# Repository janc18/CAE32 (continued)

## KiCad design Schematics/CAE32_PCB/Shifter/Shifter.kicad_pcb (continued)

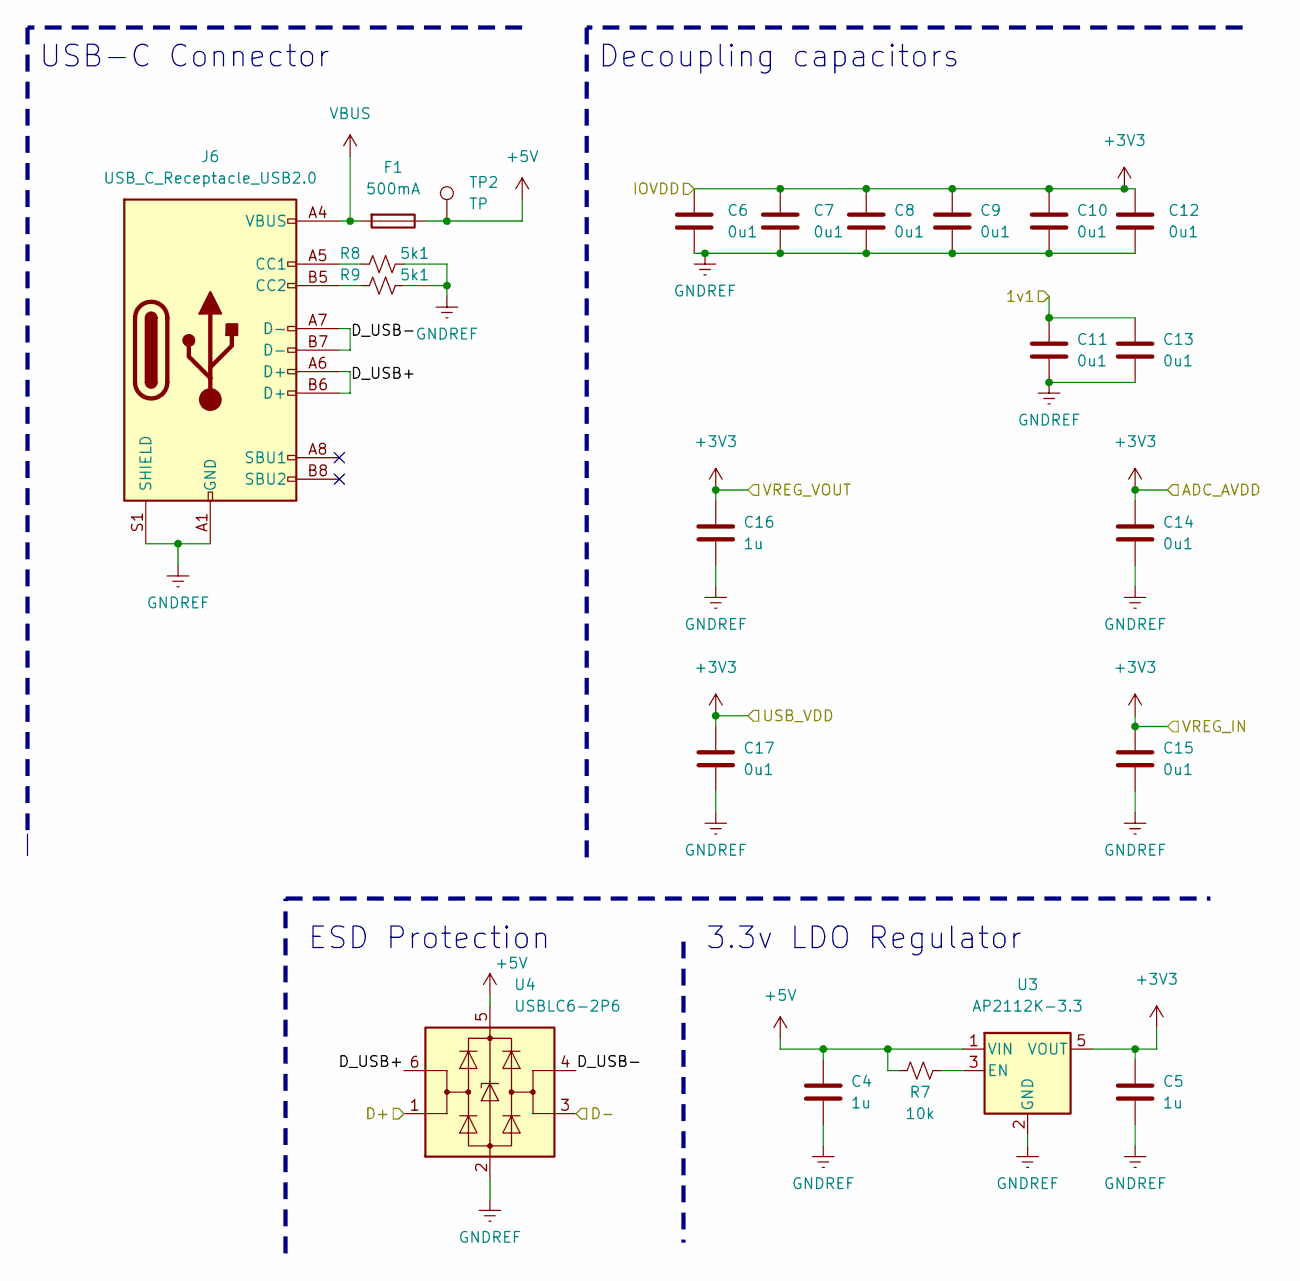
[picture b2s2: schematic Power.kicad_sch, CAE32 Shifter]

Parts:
C4, C5, C16: 1u; C_01005_0402Metric
C6, C7, C8, C9, C10, C11, C12, C13, C14, C15, C17: 0u1; C_01005_0402Metric
F1: 500mA; Fuse_0603_1608Metric
J6: USB_C_Receptacle_USB2.0; USB_C_Receptacle_Palconn_UTC16-G
R7: 10k; R_0402_1005Metric
R8, R9: 5k1; R_0402_1005Metric
TP2: TP; TestPoint_Pad_D1.0mm
U3: AP2112K-3.3; SOT-23-5
U4: USBLC6-2P6; SOT-666

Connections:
+3V3: C5.1, C6.1, C7.1, C8.1, C9.1, C10.1, C12.1, C14.1, C15.1, C16.1, C17.1, U3.5 (VOUT); also elsewhere on the board
+5V: C4.1, F1.1, R7.2, TP2.1, U3.1 (VIN), U4.5 (VBUS)
/Power/1v1: C11.1, C13.1; also elsewhere on the board
/Power/D+: U4.1 (I/O1); also elsewhere on the board
/Power/D-: U4.3 (I/O2); also elsewhere on the board
/Power/D_USB+: J6.A6 (D+), J6.B6 (D+), U4.6 (I/O1)
/Power/D_USB-: J6.A7 (D-), J6.B7 (D-), U4.4 (I/O2)
GNDREF: C4.2, C5.2, C6.2, C7.2, C8.2, C9.2, C10.2, C11.2, C12.2, C13.2, C14.2, C15.2, C16.2, C17.2, J6.A1 (GND), J6.A12 (GND), J6.B1 (GND), J6.B12 (GND), J6.S1 (SHIELD), R8.1, R9.1, U3.2 (GND), U4.2 (GND); also elsewhere on the board
unnamed: J6.A5 (CC1), R8.2
unnamed: J6.B5 (CC2), R9.2
unnamed: R7.1, U3.3 (EN)
VBUS: F1.2, J6.A4 (VBUS), J6.A9 (VBUS), J6.B4 (VBUS), J6.B9 (VBUS)

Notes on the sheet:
USB-C Connector
3.3v LDO Regulator
ESD Protection
Decoupling capacitors

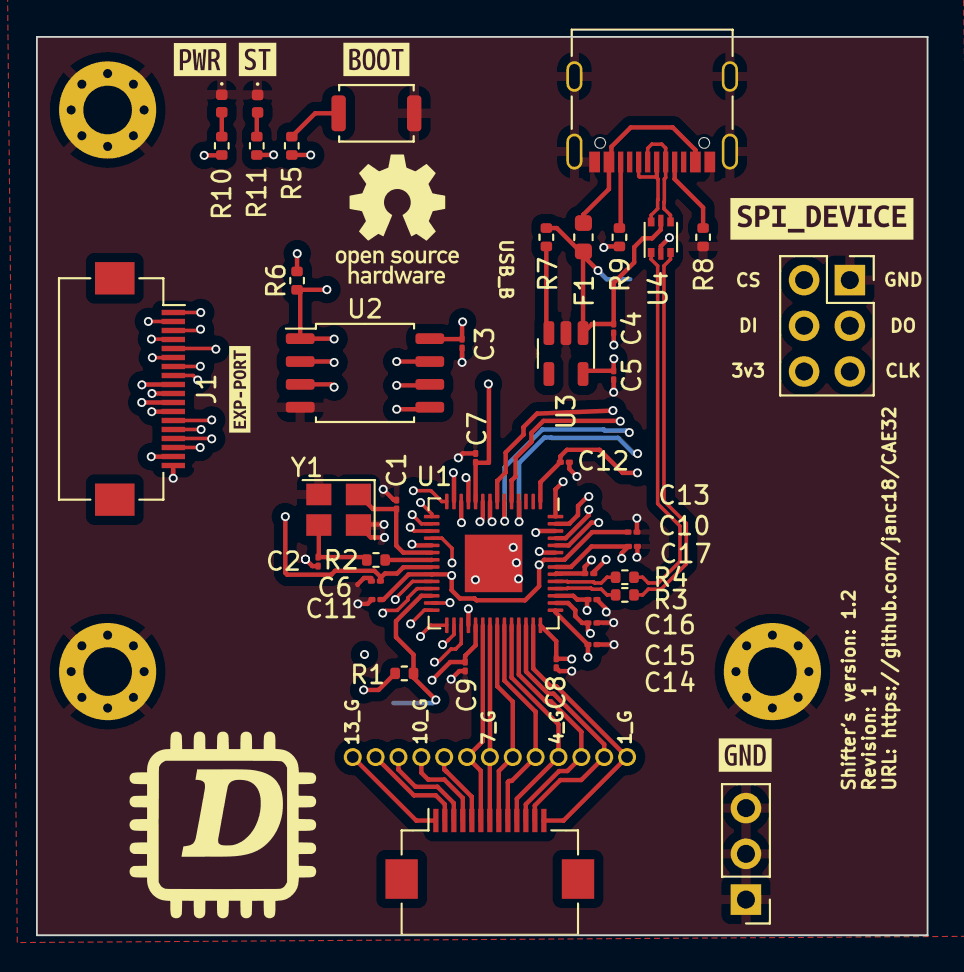
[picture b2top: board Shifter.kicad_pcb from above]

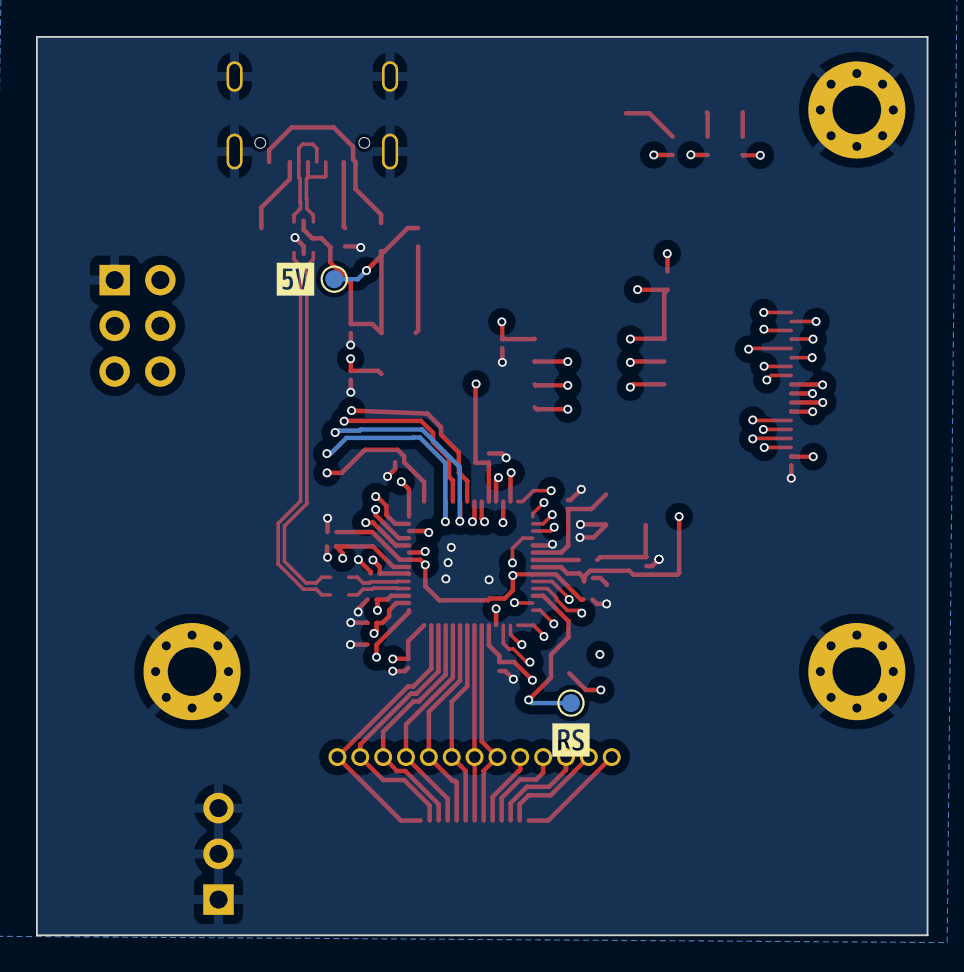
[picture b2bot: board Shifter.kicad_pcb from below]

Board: 4 copper layers, 49.5 x 49.9 mm, 56 parts (4 on the bottom side), 57 nets.

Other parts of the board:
kibuzzard-64B75D82: G***; kibuzzard-64B75D82
kibuzzard-64B759C0: G***; kibuzzard-64B759C0
kibuzzard-6511E845: G***; kibuzzard-6511E845
kibuzzard-6511E886: G***; kibuzzard-6511E886
kibuzzard-6517AD32: G***; kibuzzard-6517AD32
kibuzzard-6518B6F6: G***; kibuzzard-6518B6F6
kibuzzard-651234A4: G***; kibuzzard-651234A4
kibuzzard-651234C4: G***; kibuzzard-651234C4

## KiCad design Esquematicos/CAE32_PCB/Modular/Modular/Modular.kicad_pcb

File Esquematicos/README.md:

# Placa de constrol principal CAE32

## Como microcontrolador principal se usará el ESP-32-S3

Debido a que este cuenta con la funcionalidad OTG "On The Go", con lo cual ya no es necesario hardware extra 
para hacer la conexión.

## Elementos

* Puerto Usb tipo C para conectarlo a la Pc.

* Alimentación proveniente de Pc.

* Multiplexores.
	- Para conmutar entre las entradas analógicas y digitales, provenientes de los sensores de posicion de pedales e
interruptores correspondientes al valor de la marcha.

* ADC
	- Para obtener una mayor presición se usara un ADC externo en conjunto con el multiplexor y leer las entradas
analógicas una a la vez.

* Pines sobrantes expuestos, debido que aún es un prototipo. 

## Microcontrolador secundario

Este MCU se conectara con el microcontrolador principal por medio de UART, para controlar accesorios o incluso 
reducirle la carga al ESP32-S3, manipulando y formateando valores.

Ademas de tener todos los pines expuestos. 

## Controlador de potencia para el nema 34

Este se encontrara en otra PCB, y las señales seran producidas por el ESP32-S3 o por el MCU secundario.

## PCBs para los pedales

Se cambiara el AS5600 por un sensor de efecto Hall, así que será necesario fabricar una pequeña PCB, para sujetarlo
en su lugar y filtrar la señal en caso que se requiera

## Descripción detallada de componentes

* PCB
Para programar los dos MCU, se usará un USB-UART en caso del ESP32-S3 y Stlink para el MCU de STM

1. ESP32-S3-WROOM-1-N4 [Guía para diseño del hardware del ESP32-S3](https://www.espressif.com/sites/default/files/documentation/esp32-s3_hardware_design_guidelines_en.pdf)

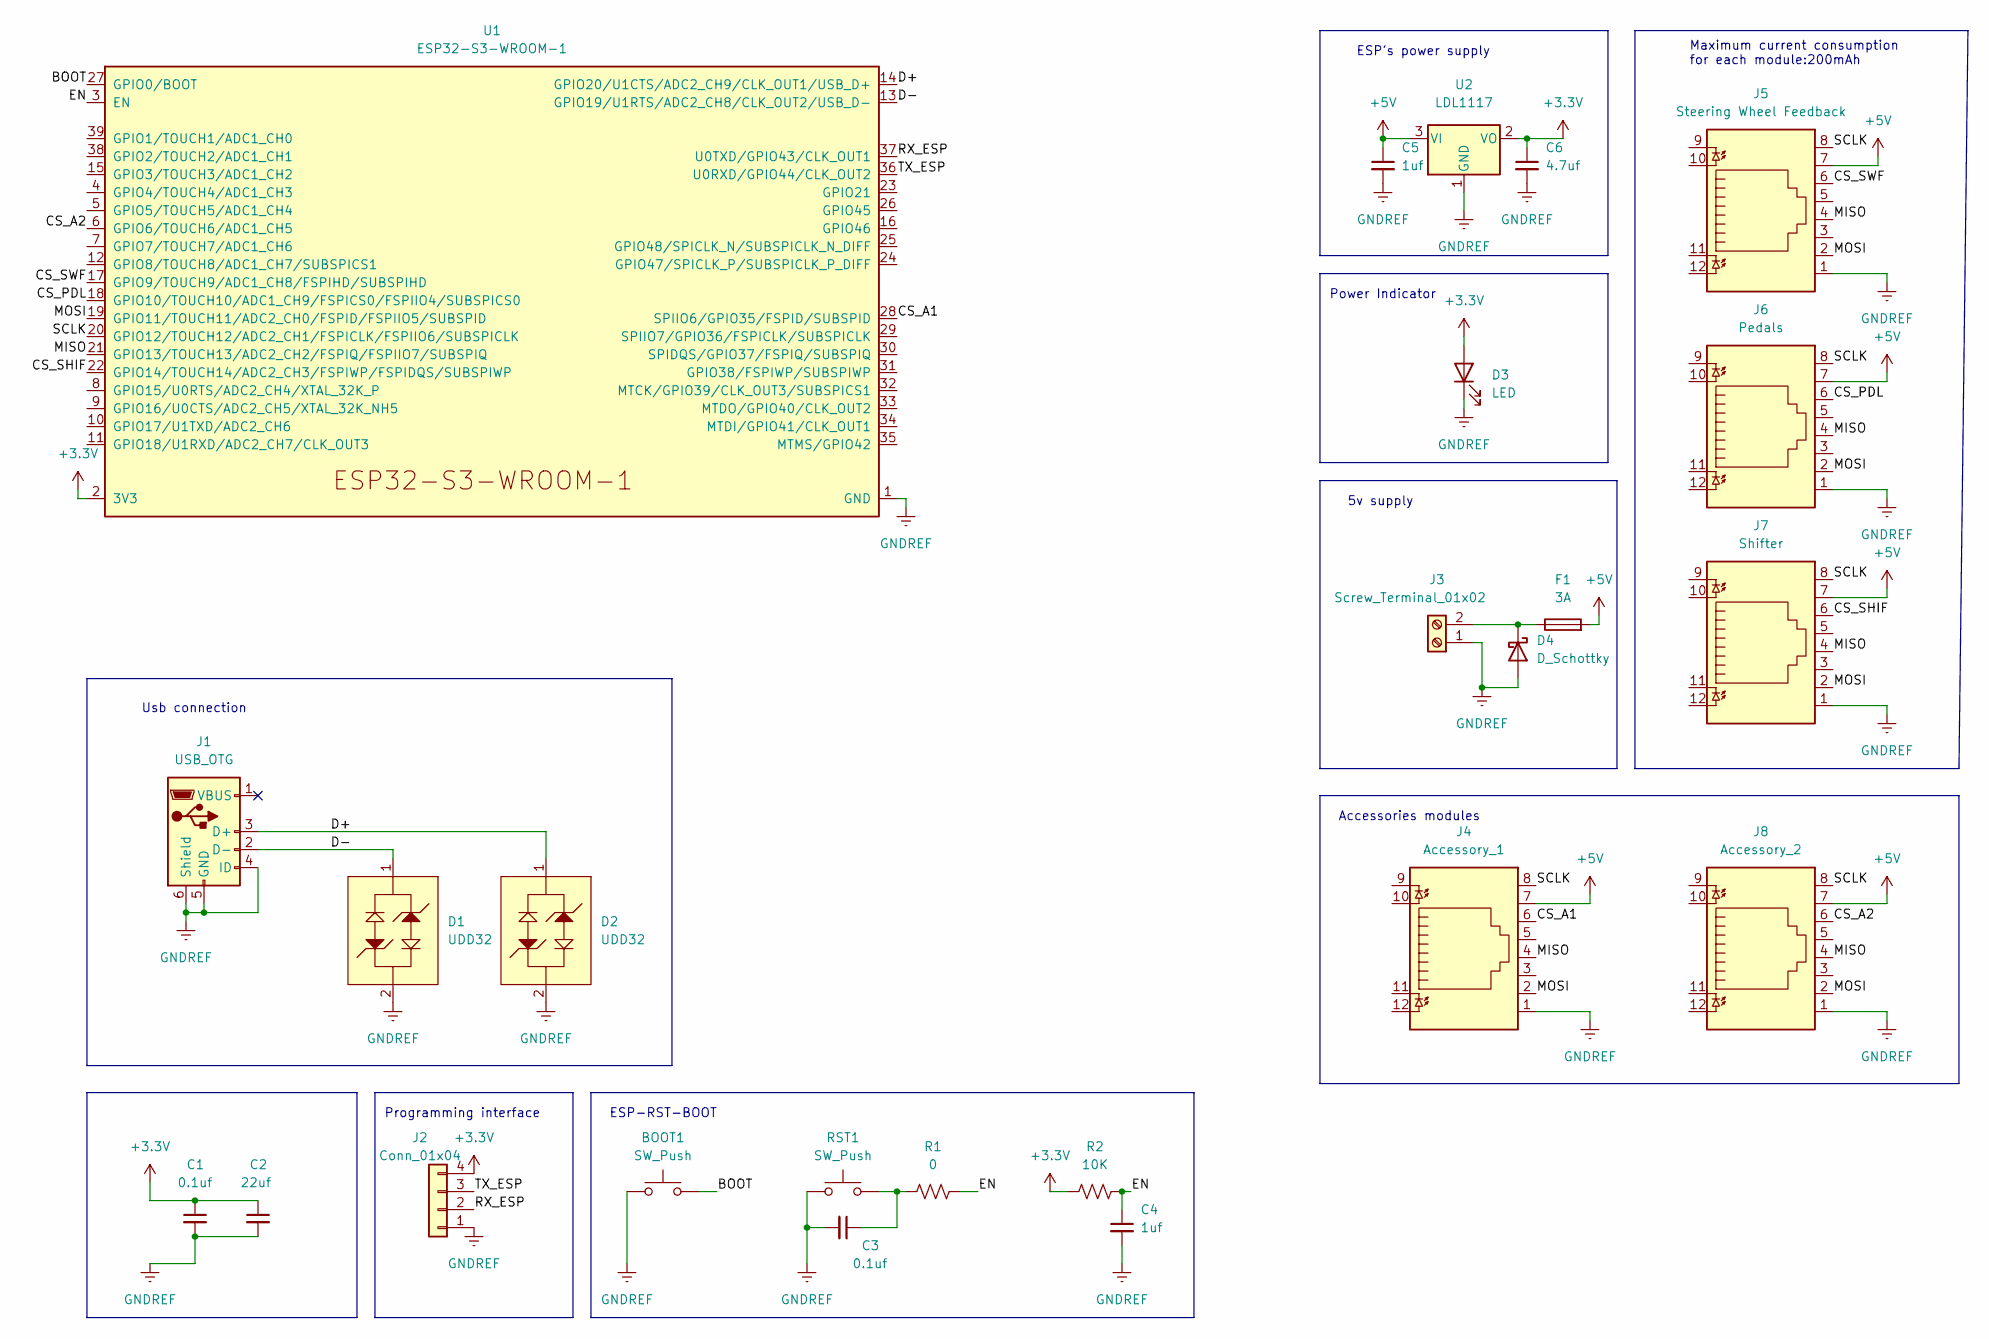
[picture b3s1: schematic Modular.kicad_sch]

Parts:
BOOT1: SW_Push; SW_Push_1P1T_NO_CK_KSC6xxJ
C1, C3: 0.1uf; C_0805_2012Metric_Pad1.18x1.45mm_HandSolder
C2: 22uf; C_0805_2012Metric_Pad1.18x1.45mm_HandSolder
C4, C5: 1uf; C_0805_2012Metric_Pad1.18x1.45mm_HandSolder
C6: 4.7uf; C_0805_2012Metric_Pad1.18x1.45mm_HandSolder
D1, D2: UDD32
D3: LED; LED_0805_2012Metric_Pad1.15x1.40mm_HandSolder
D4: D_Schottky; D_SMA_Handsoldering
F1: 3A; Fuse_1812_4532Metric_Pad1.30x3.40mm_HandSolder
J1: USB_OTG; USB_Micro-B_Amphenol_10104110_Horizontal
J2: Conn_01x04; PinHeader_1x04_P2.54mm_Vertical
J3: Screw_Terminal_01x02; TerminalBlock_bornier-2_P5.08mm
J4: Accessory_1; RJ45_Amphenol_RJHSE538X
J5: Steering Wheel Feedback; RJ45_Amphenol_RJHSE538X
J6: Pedals; RJ45_Amphenol_RJHSE538X
J7: Shifter; RJ45_Amphenol_RJHSE538X
J8: Accessory_2; RJ45_Amphenol_RJHSE538X
R1: 0; R_0805_2012Metric_Pad1.20x1.40mm_HandSolder
R2: 10K; R_0805_2012Metric_Pad1.20x1.40mm_HandSolder
RST1: SW_Push; SW_Push_1P1T_NO_CK_KSC6xxJ
U1: ESP32-S3-WROOM-1
U2: LDL1117; SOT-223-3_TabPin2

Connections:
+3.3V: C1.1, C2.1, C6.1, D3.2 (A), J2.4, R2.1, U1.2 (3V3), U2.2 (VO)
+5V: C5.1, F1.2, J4.7, J5.7, J6.7, J7.7, J8.7, U2.3 (VI)
/BOOT: BOOT1.2, U1.27 (GPIO0/BOOT)
/CS_A1: J4.6, U1.28 (SPIIO6/GPIO35/FSPID/SUBSPID)
/CS_A2: J8.6, U1.6 (GPIO6/TOUCH6/ADC1_CH5)
/CS_PDL: J6.6, U1.18 (GPIO10/TOUCH10/ADC1_CH9/FSPICS0/FSPIIO4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)
/CS_SHIF: J7.6, U1.22 (GPIO14/TOUCH14/ADC2_CH3/FSPIWP/FSPIDQS/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)
/CS_SWF: J5.6, U1.17 (GPIO9/TOUCH9/ADC1_CH8/FSPIHD/SUBSPIHD)
/D+: D2.1, J1.3 (D+), U1.14 (GPIO20/U1CTS/ADC2_CH9/CLK_OUT1/USB_D+)
/D-: D1.1, J1.2 (D-), U1.13 (GPIO19/U1RTS/ADC2_CH8/CLK_OUT2/USB_D-)
/EN: C4.1, R1.2, R2.2, U1.3 (EN)
/MISO: J4.4, J5.4, J6.4, J7.4, J8.4, U1.21 (GPIO13/TOUCH13/ADC2_CH2/FSPIQ/FSPIIO7/S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)
/MOSI: J4.2, J5.2, J6.2, J7.2, J8.2, U1.19 (GPIO11/TOUCH11/ADC2_CH0/FSPID/FSPIIO5/S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)
/RX_ESP: J2.2, U1.37 (U0TXD/GPIO43/CLK_OUT1)
/SCLK: J4.8, J5.8, J6.8, J7.8, J8.8, U1.20 (GPIO12/TOUCH12/ADC2_CH1/FSPICLK/FSPIIO6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)
/TX_ESP: J2.3, U1.36 (U0RXD/GPIO44/CLK_OUT2)
GNDREF: BOOT1.1, C1.2, C2.2, C3.2, C4.2, C5.2, C6.2, D1.2, D2.2, D3.1 (K), D4.2 (A), J1.4 (ID), J1.5 (GND), J1.6 (Shield), J2.1, J3.1, J4.1, J5.1, J6.1, J7.1, J8.1, RST1.1, U1.1 (GND), U1.40 (GND), U1.41 (GND), U2.1 (GND)
unnamed: C3.1, R1.1, RST1.2
unnamed: D4.1 (K), F1.1, J3.2

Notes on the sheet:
Maximum current consumption for each module:200mAh
Power Indicator
Usb connection
Accessories modules
5v supply
Programming interface
ESP's power supply
ESP-RST-BOOT

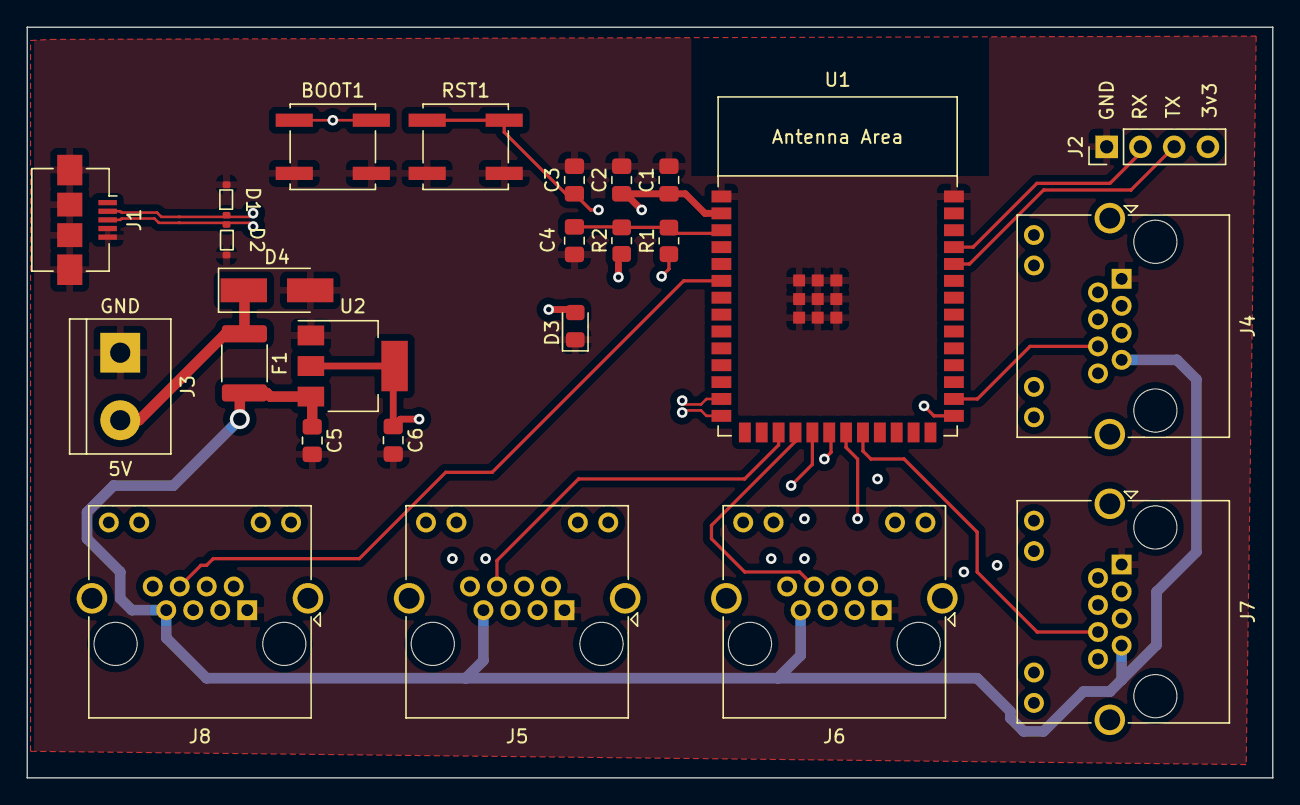
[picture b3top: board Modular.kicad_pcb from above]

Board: 4 copper layers, 93.8 x 56.5 mm, 25 parts (0 on the bottom side), 19 nets.

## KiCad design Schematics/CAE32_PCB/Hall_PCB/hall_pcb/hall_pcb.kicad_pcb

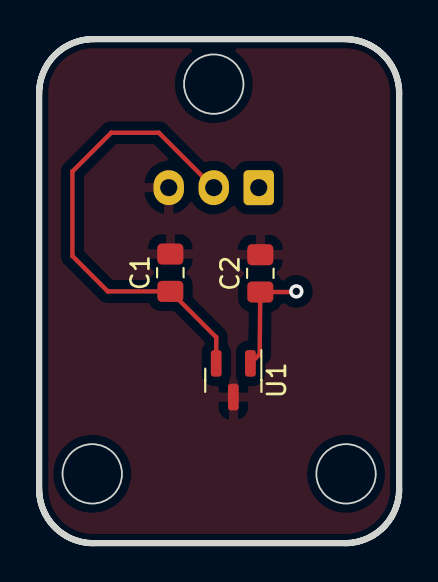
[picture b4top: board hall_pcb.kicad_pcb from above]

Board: 2 copper layers, 20.0 x 28.0 mm, 4 parts (1 on the bottom side), 3 nets.

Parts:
C1: 4.7nf; C_0805_2012Metric_Pad1.18x1.45mm_HandSolder
C2: 100nf; C_0805_2012Metric_Pad1.18x1.45mm_HandSolder
J1: Conn_01x03_Female; JST_EH_B3B-EH-A_1x03_P2.50mm_Vertical
U1: MT9105ET; SOT-23

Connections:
+3V3: C2.1, J1.1, U1.1 (VCC)
/Vout: C1.1, J1.2, U1.2 (OUTPUT)
GNDREF: C1.2, C2.2, J1.3, U1.3 (GND)

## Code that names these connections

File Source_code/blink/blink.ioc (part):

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Mcu.Name=STM32F072R(8-B)Tx
Mcu.Package=LQFP64
Mcu.UserName=STM32F072RBTx
PA11.Mode=Device
PA11.Signal=USB_DM
PA12.Mode=Device
PA12.Signal=USB_DP
PA2.Signal=GPIO_Output
PA4.GPIOParameters=GPIO_Label
PA4.GPIO_Label=CS
PA4.Signal=GPIO_Output
PA5.GPIOParameters=GPIO_Label
PA5.GPIO_Label=SCLK
PA5.Signal=GPIO_Output
PA6.GPIOParameters=GPIO_Label
PA6.GPIO_Label=MISO
PA6.Signal=GPIO_Input
PA7.GPIOParameters=GPIO_Label
PA7.GPIO_Label=MOSI
PA7.Signal=GPIO_Output
PC0.Signal=GPIO_Output
PC1.Signal=GPIO_Output
PC2.Signal=GPIO_Output
PF0-OSC_IN.Mode=HSE-External-Oscillator
PF0-OSC_IN.Signal=RCC_OSC_IN
PF1-OSC_OUT.Mode=HSE-External-Oscillator
PF1-OSC_OUT.Signal=RCC_OSC_OUT
RCC.SYSCLKFreq_VALUE=48000000
RCC.SYSCLKSource=RCC_SYSCLKSOURCE_PLLCLK
board=custom

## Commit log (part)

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2023-06-16 Primer commit
2023-06-17 delete: se elimina libreria json-c de archivo CMakeLists
2023-06-17 add: Archivo Makefile, para ejecutar la construcción de la gui
2023-06-17 update: README, con las nuevas caracteristicas de la PCB de pedales version
2023-06-17 chore: se corrigen valores de referencias de componentes, creación de nuevas hojas de diagramas, mejor distribución de componentes
2023-06-17 add: hoja de esquematicos de conexiones de alimentacion
2023-06-18 add: imagen con función de cada pin
2023-06-18 update: se añade otra hoja para las celdas de carga, ademas de reorganizar todas las hojas
2023-06-18 update: se agrega instrucciones para la compilacion de la GUI usando docker
2023-06-19 update: Se nombran los pines con sus funciones
2023-06-20 add: se crea archivo idf_component.yml con la depencia necesaria (esp_tinyusb)
2023-06-20 fix: se corrige el nombre de la depencia en require de tinyusb->esp_tinyusb, ademas de añadir las depencia de freertos
2023-06-20 chore: se corrige el estilo de codigo
2023-06-20 delete: component.mk, ya que no es necesario
2023-06-21 update: se agrega el consumo de corriente a los IC's ademas de agregar el URL y numero de parte de los componentes de LCSC en kicad
2023-06-21 add: archivo de contribución en español
2023-06-21 add: se añade nueva regla para contruir la gui
2023-06-21 Update README.md
    remove: imagen de PCB terminada
2023-06-22 add: imagen de logo de oshw y easter egg
2023-06-25 add: nuevas reglas de archivos gerber, csv, xml y .log
2023-06-25 add: se añade un fusible extra para proteger el circuito de 5v al regulador de voltage de 3v3
2023-06-25 update: README.md con imagen de la version 2 de PCB para los pedales
2023-06-26 update: se agrega via stitching a la pcb de los pedales
2023-07-12 delete: archivos innecesarios
2023-07-12 add:makefile para construir el firmware usando docker
2023-07-16 add: nueva regla para los realeases de archivos de frabricacion pcb
2023-07-21 update: se enruta completamente la pcb, aunque aun necesario un análisis posterior, ademas de agregar huellas e imagen de la pcb completa
2023-09-16 update: changed the castelled holes for pin sockets and changed 0603 footprints to 0402
2023-09-20 update: added templates files for the devolpment of a Feedback PCB
2023-09-20 chore: arrange of schematic elements
2023-09-24 update: new desing for the PCB edgecuts
2023-09-27 update: added new information about the pcb updates, and created another README file in English
2023-09-27 update: added a new rule to exclude new realeses
2023-09-27 update: added minor improvements to Pedal's PCB
2023-09-27 add: new rule for lck files
2023-10-01 update: redesign of the shifter PCB, changing the PCB requirements(via from 0.15 to 0.3mm) and pin sockets for FCP connectors
2023-10-02 remove: deleted README file in the "Esquematicos" folder because is irrelevant
2023-10-02 update: Device simulation's README file changed to English
2023-10-02 update: ESP32-S3's README file changed to English
2023-10-03 test: testing Github Actions to test the GUI compilation
2023-10-29 chore: update README, added PCB result image
2023-11-06 chore: update README with the overall status of the project
2023-11-27 add: UML use cases draft using the umbrellon software
2023-11-29 update: finished UML use cases diagram
2023-11-29 add: UML use cases image
2023-12-01 chore: added two new "Section" with a brief function resume and a Pcb issues
2023-12-16 deleted: umbrello file for the generation of an UML diagram
2023-12-16 chore: added file to write notes about the whole project
2023-12-16 chore: creation of a file to take notes about the how can be implement the TDD to the project
2023-12-18 add: a simple c code that print a string from another path
2023-12-18 add: c code that compare a string
2023-12-18 add: cmake file for future device descriptor testing
2023-12-18 update: included device descriptor library
2023-12-19 add: Makefile to prepare and compile any project(GUI and test cases)
2023-12-19 add: README.md file for a brief explication of the contents at Codigo folder
2023-12-21 rename: configs section to Shared_libraries
2023-12-25 chore: added comment to do a double check for pkg-config and pkgconfig
2023-12-25 add: extern variable and headers guards
2023-12-25 fix: cmake device descriptor paths
2023-12-27 update: added function to get a line token
2023-12-27 add: a simple example of how can be used the new functions created(tokens)
2023-12-28 update: refactor and added the find_object function
2023-12-28 add: initialized some variables, testing memory leaks
2023-12-29 refactor: removed inecessary functions, tested for memory leaks, and added comments
2023-12-29 add: get_each_line_of_string prototype
2023-12-29 update: added example of how get each line from the file string
2023-12-30 update: removed all testing code
2023-12-30 update: complete get_file_token function, now it can get all the tokens and of the file
2023-12-30 chore: added new line between objects
2023-12-31 update: added a example of how get all the tokens for processing
2023-12-31 chore: updated function prototype of get_file_tokens and added a function to fre get_file_tokens memory
2023-12-31 fix: moved the constant char values from .h to .c file
2023-12-31 chore: added how to test the program and an input test file
2024-01-01 chore: added the steering wheel object
2024-01-01 chore: added prototypes functions
2024-01-02 chore: moved .c and .h file to their respectives folders src and include
2024-01-02 update: added the necessary elements to perform unit cases
2024-01-02 chore: tested get_objects_index function
2024-01-02 update: added a CMakeLists.txt file to build the device_descriptor executable
2024-01-03 update: added a debug flag
2024-01-03 chore: removed stdbool lib
2024-01-06 rename: device_input_file.cpp -> device_input_file.h
2024-01-06 update: include stdbool library
2024-01-06 refactor: remove_extra_spaces function
2024-01-08 update: Memory has sucessfully free from all the tests
2024-01-11 update: added a function to free memory resources from when get_array_of_strings function it is called
2024-01-11 update: added a new function to free memory resources generate by the function "get_array_of_tokens_from_an_string_array"
2024-01-11 update: included preprototypes function to free memory resources
2024-01-11 update: added tokens functions
2024-01-11 update: function prototypes
2024-01-11 chore: added another c file source to the tests
2024-01-13 refactor: replaced DEBUG context with fprintf to stderr, and created a function to detect if the string is empty
2024-01-13 refactor: replace context DEBUG with fprintf, now redirect any error to stderr
2024-01-13 update: PCB pedals Version:2.1.1
2024-01-16 chore: Moved all the Pedals contents a folder above and updated pcb including the required oscilator
2024-01-16 chore: update the schematics to the 7.0 kicad version
2024-01-16 rename: Esquematicos->Schematics folder
2024-01-27 update: added new path for the setup script
2024-01-27 delete: examples of how to use cmake
2024-01-27 add: Device simulation CMakeLists.txt
2024-02-03 chore: Example code in how to use the parser
2024-02-05 chore: deleted funcion for getting all the objects
2024-02-05 update: improved line debug messages, adding an error enum with some predifined errors
2024-02-05 refactor: change name for one more descriptive
2024-02-05 chore: update function prototype and added a new one (token_error)
2024-02-05 chore: added function to print the values of some object
2024-02-05 chore: update function prototype
2024-02-05 chore: format code
2024-02-05 chore: delete demo functions
2024-02-05 update: added test code to get all the object index in an array
2024-02-05 update: added demo example
2024-02-06 update: added fixed size to Keyword array
2024-02-06 fix: added array size of Keywords an removed "Start" and "End" elements
2024-02-06 update: added function to print all the objects
2024-02-06 chore: added comment
2024-02-07 dependency: added libudev
2024-02-07 chore: add implementation of libudev functions
2024-03-01 fix: changed target system to search for a device from usb to hid
2024-03-03 update: remove udev functions and variables
2024-03-03 chore: added empty files to do struct manipulation, it's an abstraction
2024-03-05 update: added parameters verifications
2024-03-06 chore: added source code to do abastractions from the token and parser function
2024-03-06 add: get_feature_value_from_device_c32_file function prototype
2024-03-06 add: functions to get features from file
2024-03-09 add: get_report_descriptor function
2024-03-09 add: get_object_name prototype function
2024-03-09 fix: change search device function, now return a string with the correct path of the device
2024-03-14 add: evdev dependency and remove uvdev
2024-03-14 refactor: changed generate_hid_path function name to generate_path
2024-03-14 add: read_event.h header file
2024-03-14 chore: add print_data function
2024-03-16 update: Pedals report descriptor
2024-03-16 chore: removed hid-example comments
2024-05-27 update: now it can check if gtk3 is istalled
2024-05-28 chore: added instructions of how to compile the project
2024-05-29 update: added flag to generate the compile commands file automatically
2024-06-01 chore: updated badgets description and contributing information
2024-06-01 updated: changed kicad version "8"
2024-06-01 refactor: code style
2024-06-03 added: function at device_descriptor.c file, to check if it's executed as sudo user
2024-06-03 added: check if the path exist
2024-06-04 chore: applied style code
2024-06-05 chore: added example of how read the descriptor and how to compare with an axis identificators
2024-06-05 chore: updated style code
2024-06-05 added: New empty files for events analysis
2024-06-05 remove: README-english.md
2024-06-05 chore: added enum with the axis event type
2024-06-22 renamed: Source Code to Source_code
2024-06-22 chore: moved the interface graphics script to Source_code/Interfaz_grafica/Interfaz_gtk
2024-06-30 chore: added prototype handle_signal function
2024-06-30 chore: added signals (SIGINT) to stops the threads
2024-07-01 removed: moved functions used to check if the program was executed as sudo user to the setup library
2024-07-01 refactor: improved readability through function conolidation
2024-07-28 fix: added -f flag to clean the build files at Makefile
2024-08-09 update: now display correctly the device current events in the terminal
2024-08-11 chore: initialize device_handle struct to null and added a call to free all the memory
2024-08-11 fixed: added instructions to free memory
2024-08-18 chore: update comments and added comments
2024-08-18 chore: added error message when the threads are created
2024-08-18 fixed: segmentation fault, changing calloc from malloc
2024-09-01 updated: Pcb design, fixed plane grounds and minor improvements, added stlink connector, updated BOM with the current market stock
2024-09-11 added: guard to check if the device handle is NULL, and formating text
2024-09-11 chore: added max size of values array
2024-09-11 update: Now it prints the current id event
2024-10-01 fixed: changed fuse footprint for the correct one(0805)
2024-10-26 add: Stm32HID Pedals project
2024-10-26 fixed: changed fuse footprint to 1206
2024-11-19 Report descriptor funcionando
2024-12-16 chore: remove extra characters in main.c
2024-12-16 fixed: paths for the GUI setup
2024-12-17 chore: changed input parameter for the correct one char *
2024-12-30 fixed: allocation for event name
2025-01-02 chore: changed escape sequences and added information messages
2025-01-02 added: flags for the compiler to check for extra warnings
2025-01-02 chore: changed and initialize variables
2025-01-02 update: improve terminal printing with colors and format
2025-02-03 deleted: comments and updateAxis function
2025-03-26 updated: device descriptors
2025-03-26 updated: added raylib dependency
2025-04-13 updated: now it can get all the 3 values frm the ADC (accel,brake and clutch)
2025-04-19 updated: now display correctly the channels to the bars
2025-07-05 fixed: adc128 pin spacing
